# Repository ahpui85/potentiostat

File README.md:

This project is aimed to design a miniaturized, an inexpensive, and easy to use electrochemical potentiostat to meet the demand for on-site measurement. Integration of the potentiostat to a mobile device makes the measuring device portable. Bluetooth technology is chosen to communicate with mobile device as it features both low power and wireless communication. Therefore the potentiostat consist of the following modules: 
a) Front-end module which drives the sensor and the measures the current. 
b) power module that generates the stable voltage. 
c) A back-end module comprised of microcontroller (MCU) to control voltage, digitize and process the data, and Bluetooth module to communicate with the mobile devices. 
We have created a guide to design, layout, assemble, troubleshoot, and test a Printed circuit board (PCB) that is able conduct electrochemistry measurement. This step by step guide will ultimately allow anyone to develop a portable, accessible, and low-cost potentiostat based on Arduino, together with mobile phone application to control the potentiostat.

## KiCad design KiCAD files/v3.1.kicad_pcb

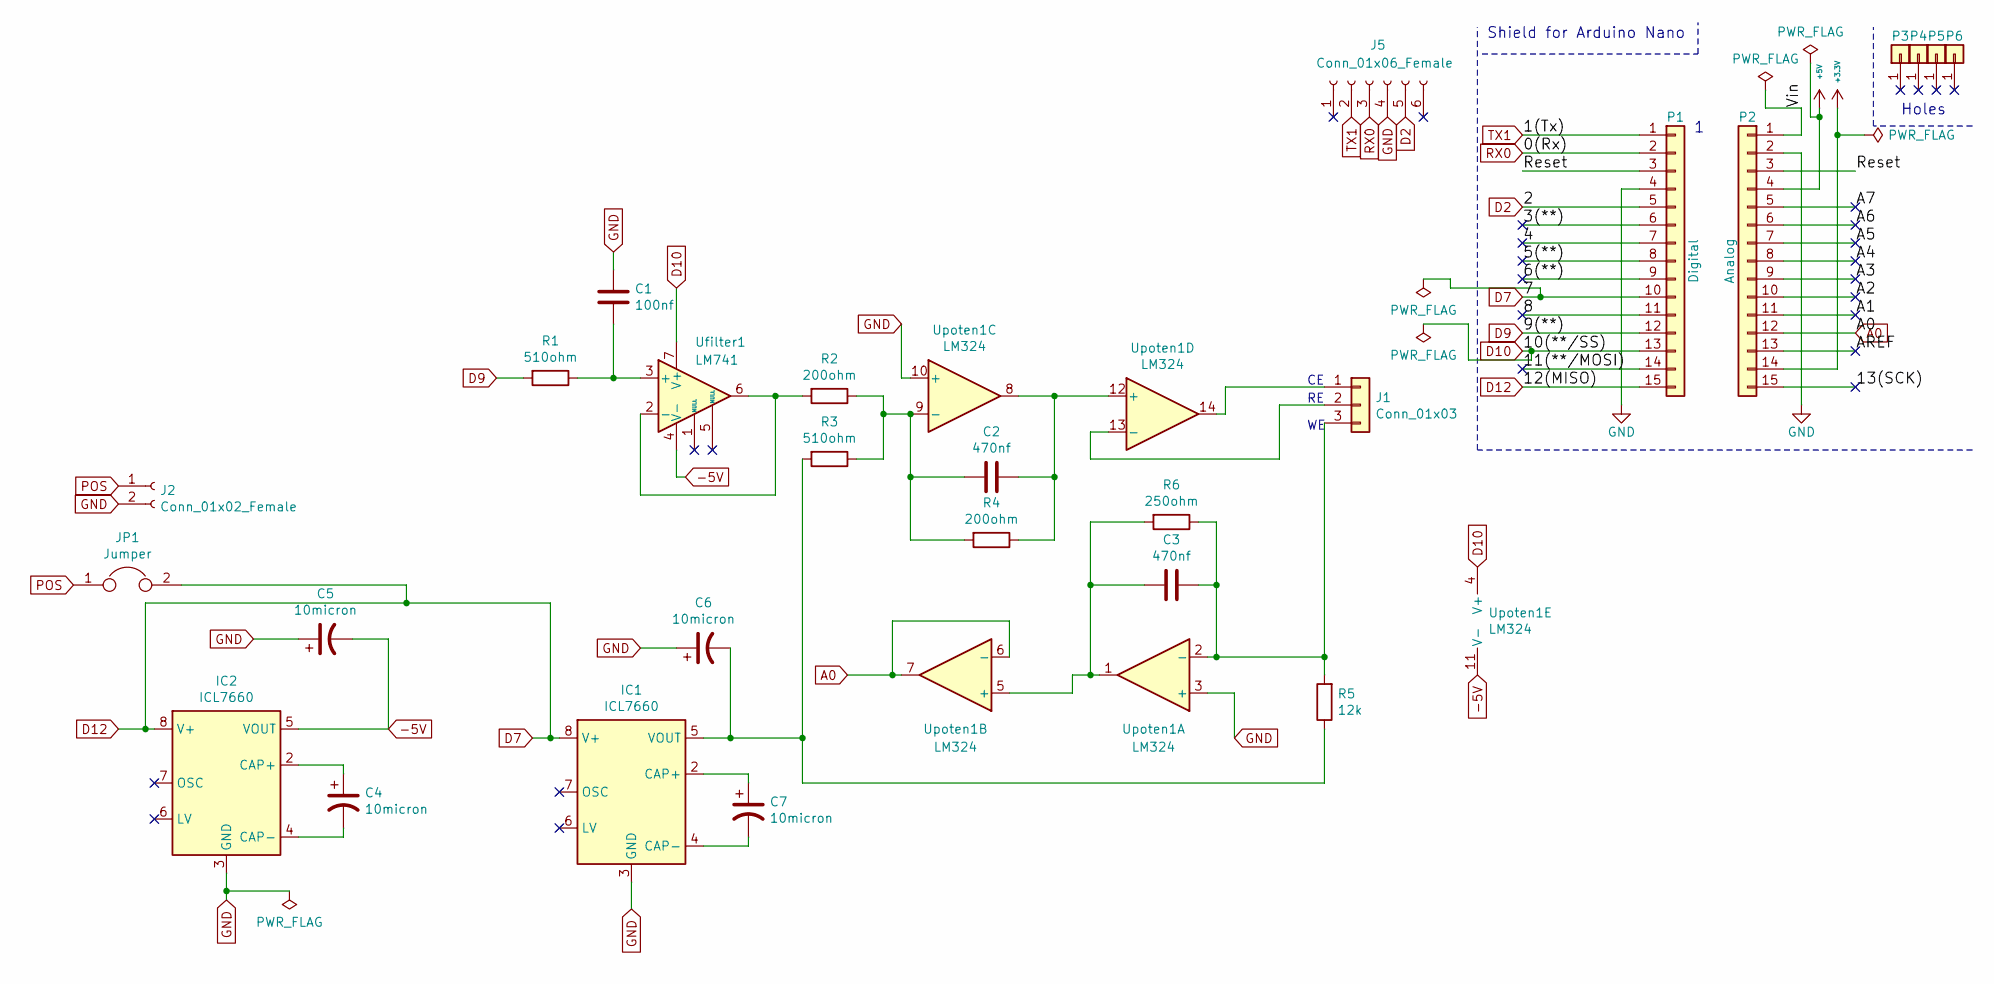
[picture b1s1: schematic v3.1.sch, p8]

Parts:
C1: 100nf; C_Axial_L3.8mm_D2.6mm_P7.50mm_Horizontal
C2, C3: 470nf; C_Axial_L3.8mm_D2.6mm_P7.50mm_Horizontal
C4, C5, C6, C7: 10micron; CP_Radial_D5.0mm_P2.00mm
IC1, IC2: ICL7660; DIP-8_W7.62mm
J1: Conn_01x03; PinHeader_1x03_P2.54mm_Vertical
J2: Conn_01x02_Female; PinSocket_1x02_P2.54mm_Vertical
J5: Conn_01x06_Female; PinSocket_1x06_P2.54mm_Vertical
JP1: Jumper; TestPoint_2Pads_Pitch2.54mm_Drill0.8mm
P1: Digital; Socket_Strip_Arduino_1x15
P2: Analog; Socket_Strip_Arduino_1x15
P3, P4, P5, P6: CONN_01X01; 1pin_Nano
R1, R3: 510ohm; R_Axial_DIN0204_L3.6mm_D1.6mm_P7.62mm_Horizontal
R2, R4: 200ohm; R_Axial_DIN0204_L3.6mm_D1.6mm_P7.62mm_Horizontal
R5: 12k; R_Axial_DIN0204_L3.6mm_D1.6mm_P7.62mm_Horizontal
R6: 250ohm; R_Axial_DIN0204_L3.6mm_D1.6mm_P7.62mm_Horizontal
Ufilter1: LM741; DIP-8_W7.62mm
Upoten1: LM324; DIP-14_W7.62mm

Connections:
+3V3: P2.14
+5V: P2.4
-5V: C5.2, IC2.5 (VOUT), Ufilter1.4 (V-), Upoten1.11 (V-)
/3(**): P1.6
/4: P1.7
/5(**): P1.8
/6(**): P1.9
/8: P1.11
/11(**/MOSI): P1.14
/13(SCK): P2.15
/A1: P2.11
/A2: P2.10
/A3: P2.9
/A4: P2.8
/A5: P2.7
/A6: P2.6
/A7: P2.5
/AREF: P2.13
/Reset: P1.3, P2.3
/Vin: P2.1
A0: P2.12, Upoten1.6 (-), Upoten1.7
D2: J5.5, P1.5
D9: P1.12, R1.2
D10: P1.13, Ufilter1.7 (V+), Upoten1.4 (V+)
D12: IC1.8 (V+), IC2.8 (V+), JP1.2, P1.10, P1.15
GND: C1.1, C5.1, C6.1, IC1.3 (GND), IC2.3 (GND), J2.2, J5.4, P1.4, P2.2, Upoten1.3 (+), Upoten1.10 (+)
unnamed: C1.2, R1.1, Ufilter1.3 (+)
unnamed: C2.1, R4.1, Upoten1.8, Upoten1.12 (+)
unnamed: C2.2, R2.1, R3.1, R4.2, Upoten1.9 (-)
unnamed: C3.1, J1.3, R5.2, R6.1, Upoten1.2 (-)
unnamed: C3.2, R6.2, Upoten1.1, Upoten1.5 (+)
unnamed: C4.1, IC2.2 (CAP+)
unnamed: C4.2, IC2.4 (CAP-)
unnamed: C6.2, IC1.5 (VOUT), R3.2, R5.1
unnamed: C7.1, IC1.2 (CAP+)
unnamed: C7.2, IC1.4 (CAP-)
unnamed: J1.1, Upoten1.14
unnamed: J1.2, Upoten1.13 (-)
unnamed: R2.2, Ufilter1.2 (-), Ufilter1.6
POS: J2.1, JP1.1
RX0: J5.3, P1.2
TX1: J5.2, P1.1

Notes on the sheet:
Shield for Arduino Nano
Holes

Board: 2 copper layers, 27 parts (0 on the bottom side), 24 nets, no tracks yet.
